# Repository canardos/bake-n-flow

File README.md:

# Bake-n-Flow

## Yet another (STM32F1-based) toaster reflow oven controller - PCB design and firmware

> [!Warning]
> This is personal project. It was built and works without issue for my purposes. It is made public here in case some part of it is useful to others, but **neither the hardware nor firmware have been rigorously tested**.

**Features:**

- Customizable profiles
- Reflow / baking operations
- Manual override controls
- Touch screen control

**This repo contains the firmware and PCB design.**

**See [custom electronics projects at DuckToast.com](https://www.ducktoast.com/blog/electronics-projects/) for full project details.**

https://github.com/canardos/bake-n-flow/assets/14832310/401d4c1e-f360-4829-90d8-4b5ea61bf341

## Build

The project uses the [PlatformIO](https://platformio.org/) dependency management/build system. If you have PlatformIO installed, executing the `run` command in the root folder *should* 🙏 be all that is required for a successful build. The `platformio.ini` file contains the required configuration and PlatformIO will download the required dependencies and toolchain.

**1. Clone repo and download submodules**

```shell
> git clone https://github.com/canardos/bake-n-flow.git
> cd bake-n-flow
> git submodule update --init
```

**2. Build firmware (PlatformIO must be installed)**

```shell
> pio run

Processing release (platform: ststm32; board: genericSTM32F103VD; framework: cmsis)
-----------------------------------------------------------------------------------
Verbose mode can be enabled via `-v, --verbose` option
CONFIGURATION: https://docs.platformio.org/page/boards/ststm32/genericSTM32F103VD.html
PLATFORM: ST STM32 (19.7.0) > STM32F103VD (64k RAM. 384k Flash)
HARDWARE: STM32F103VDT6 72MHz, 64KB RAM, 384KB Flash
DEBUG: Current (stlink) External (blackmagic, cmsis-dap, jlink, stlink)
PACKAGES:
 - framework-cmsis @ 2.50501.200527 (5.5.1)
 - framework-cmsis-stm32f1 @ 4.3.5
 - tool-ldscripts-ststm32 @ 0.2.0
 - toolchain-gccarmnoneeabi @ 1.120301.0 (12.3.1)
LDF: Library Dependency Finder -> https://bit.ly/configure-pio-ldf
LDF Modes: Finder ~ chain, Compatibility ~ soft
Found 4 compatible libraries
Scanning dependencies...
Dependency Graph
|-- libpekin @ 0.2.1
|-- libpekin_stm32
Building in release mode
Compiling piobuild/build/release/FrameworkCMSIS/gcc/startup_stm32f103xe.o
...
...
...
Archiving piobuild/build/release/lib7bf/libpekin_stm32.a
Indexing piobuild/build/release/lib7bf/libpekin_stm32.a
Archiving piobuild/build/release/lib72d/libpekin.a
Indexing piobuild/build/release/lib72d/libpekin.a
Linking piobuild/build/release/firmware.elf
Checking size piobuild/build/release/firmware.elf
Advanced Memory Usage is available via "PlatformIO Home > Project Inspect"
RAM:   [========= ]  95.0% (used 62248 bytes from 65536 bytes)
Flash: [=====     ]  50.5% (used 198660 bytes from 393216 bytes)
============================= [SUCCESS]
```

**3. Upload to device**

Similarly, use `pio run --target upload` to upload the firmware to the device. You'll likely need to update the upload settings in `platformio.ini` to reflect your settings, or use your own upload tool.

```shell
> pio run --target upload

Configuring upload protocol...
AVAILABLE: blackmagic, dfu, jlink, serial, stlink
CURRENT: upload_protocol = stlink
Uploading piobuild/build/release/firmware.elf
xPack OpenOCD, x86_64 Open On-Chip Debugger 0.10.0+dev-00378-ge5be992df (2020-06-26-09:27)
Licensed under GNU GPL v2
For bug reports, read
        http://openocd.org/doc/doxygen/bugs.html
debug_level: 1

hla_swd
target halted due to debug-request, current mode: Thread
xPSR: 0x01000000 pc: 0x0800108c msp: 0x20010000
** Programming Started **
** Programming Finished **
** Verify Started **
** Verified OK **
** Resetting Target **
shutdown command invoked
======================== [SUCCESS] Took 12.58 seconds =================================
```

**4. [optional] Create project files for IDE**

If you want to view/edit the project in your favorite IDE, use PlatformIO to generate the appropriate setup/workspace files and then import the project in the IDE:

```shell
> pio project init --ide [atom|clion|codeblocks|eclipse|emacs|netbeans|qtcreator|sublimetext|vim|visualstudio|vscode]
```

See the [PlatformIO documentation](https://docs.platformio.org) for further details.

### Using an alternate build system

**Platform dependencies**

If you wish to use a different build system, you will need:

| | |
|-|-|
| ST STM32 CMSIS headers | Peripheral/register definitions |
| CMSIS headers/source | CMSIS HAL functionality - SysTick_Config, NVIC_xxx etc.|
| CMSIS Cortex-M3 system source | `SystemInit()`/`SystemCoreClockUpdate()` implementation and `SystemCoreClock`|
| Startup source file | ASM file containing the startup code and vector table |
| Linker script | Tells the linker how to setup everything in flash/SRAM |

All of these are available in the [STM32 SDK](https://www.st.com/en/development-tools/stm32-software-development-tools.html) available from ST Micro.

**Compiling / linking**

`platformio.ini` lists the required compiler flags. Be sure to use `--specs=nano.specs` and `--specs=nosys.specs` when linking using your own tools, as the standard lib is be too large and is not used.

### Compiler

The project was compiled and tested with ~~`gcc-arm-none-eabi 9.2.1`~~ `gcc-arm-none-eabi 12.3.1`. It should work with any later GCC version and possibly with other compilers. The code contains some GCC flags and some C99 VLAs.

### Target requirements

| | |
|-|-|
|MCU  | STM32F103 with FSMC |
|Flash| >195kb              |
|SRAM | >61kb               |

It may be possible to get by with less SRAM by using a smaller drawing buffer (currently 40 lines - 38.4 kb)

## Dependencies

**CMSIS**

PlatformIO should automatically include/link the correct headers/sources from the STM32 SDK.

**LVGL**

[LVGL](https://github.com/lvgl/lvgl) v5.3 (git commit `9f216a55be65ec05c477ac55f73a6efad50f7680`) is used. It is included ~~as a Git submodule~~ in the`src/lvgl` folder.

**Libpekin**

[Libpekin](https://github.com/canardos/libpekin) is a collection of shared MCU-related code resulting from this and other projects. It's included as a Git submodule in the `lib` folder. PlatformIO will include the `lib` subfolders automatically.

## Hardware - PCB

The PCB was designed with KiCad v.5, but the files have been upgraded to v.7 and are located in `/hardware/pcb`. Gerber output for the first and only revision is located in `/hardware/pcb/plots`.

**The design contains minor errors** that should be fixed if it is (re)produced. See the [blog post here](https://www.ducktoast.com/blog/electronics-projects/reflow-oven/building-a-toaster-reflow-oven-part-3-manufacturing/#pcb-errors-and-things-i-would-have-done-differently) for details.

## Folder structure

```
BakeNFlow
|
+--hardware          | KiCad schematic and board design files
|
+--lib
|  |
|  +--libpekin       | Libpekin platform independent code
|  +--libpekin_stm32 | Libpekin STM32 specific code
|
+--src
|  |
|  +--audio_samples  | Audio sample data
|  +--devices        | Hardware device drivers
|  +--lvgl           | LVGL project
|  +--lvgl_driver    | Display/touch driver for LVGL
|  +--oven           | Oven hardware interface and state management
|  +--reflow         | Reflow data structures and state management
|  +--hal            | (exception handlers etc.)
|  +--ui             | UI code for LVGL
|
|--test              | No tests in use
```

## License

This software is available under the [MIT license](https://opensource.org/license/MIT).

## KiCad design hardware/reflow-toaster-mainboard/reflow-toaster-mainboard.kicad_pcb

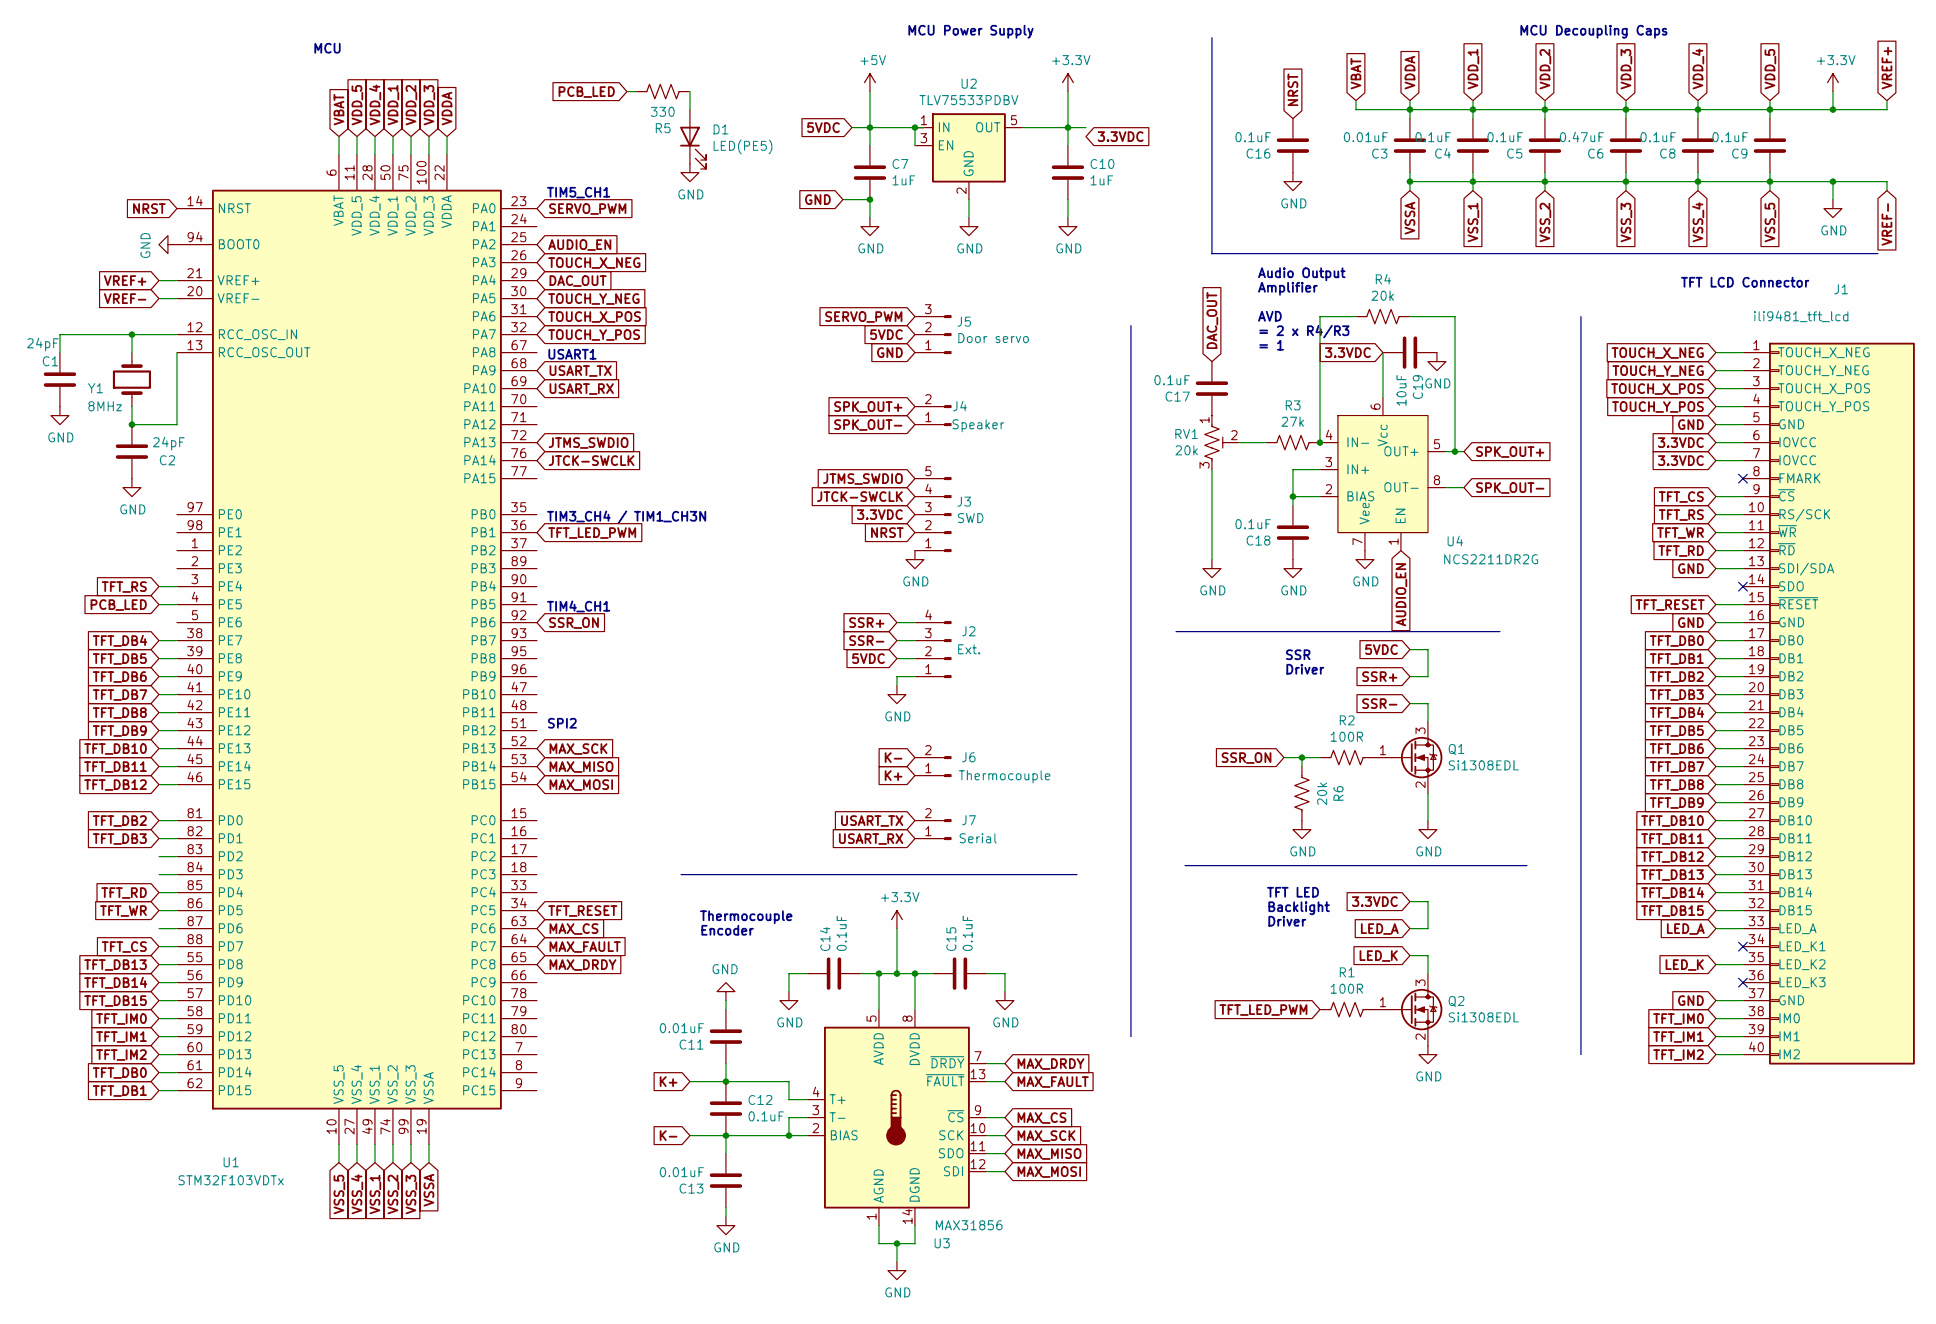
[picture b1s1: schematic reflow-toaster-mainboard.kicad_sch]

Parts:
C1, C2: 24pF; C_0402_1005Metric
C3, C11, C13: 0.01uF; C_0402_1005Metric
C4, C5, C8, C9, C12, C14, C15, C16, C17, C18: 0.1uF; C_0402_1005Metric
C6: 0.47uF; C_0402_1005Metric
C7, C10: 1uF; C_0402_1005Metric
C19: 10uF; C_0805_2012Metric
D1: LED(PE5); D_0603_1608Metric
J1: ili9481_tft_lcd; Hirose_FH12-40S-0.5SH_1x40-1MP_P0.50mm_Horizontal
J2: Ext.; PinHeader_1x04_P2.54mm_Horizontal
J3: SWD; PinHeader_1x05_P2.54mm_Horizontal
J4: Speaker; JST_PH_S2B-PH-K_1x02_P2.00mm_Horizontal
J5: Door servo; PinHeader_1x03_P2.54mm_Horizontal
J6: Thermocouple; PinHeader_1x02_P2.54mm_Horizontal
J7: Serial; PinHeader_1x02_P1.27mm_Horizontal
Q1, Q2: Si1308EDL; SOT-323_SC-70
R1, R2: 100R; R_0603_1608Metric
R3: 27k; R_0603_1608Metric
R4, R6: 20k; R_0603_1608Metric
R5: 330; R_0603_1608Metric
RV1: 20k; Trimmer_Potentiometer_Panasonic_EVM3W
U1: STM32F103VDTx; LQFP-100_14x14mm_P0.5mm
U2: TLV75533PDBV; SOT-23-5
U3: MAX31856; TSSOP-14_4.4x5mm_P0.65mm
U4: NCS2211DR2G; SOIC-8_3.9x4.9mm_P1.27mm
Y1: 8MHz; Crystal_SMD_7050-2Pin_7.0x5.0mm_HandSoldering

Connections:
5VDC: C7.1, J2.2, J2.4, J5.2, U2.1 (IN), U2.3 (EN)
AUDIO_EN: U1.25 (PA2), U4.1 (EN)
DAC_OUT: C17.2, U1.29 (PA4)
GND: C1.1, C2.1, C3.1, C4.1, C5.1, C6.1, C7.2, C8.1, C9.1, C10.2, C11.2, C13.1, C14.1, C15.2, C16.1, C18.1, C19.1, D1.1 (K), J1.5 (GND), J1.13 (SDI/SDA), J1.16 (GND), J1.37 (GND), J2.1, J3.1, J5.1, Q1.2 (S), Q2.2 (S), R6.1, RV1.3, U1.10 (VSS_5), U1.19 (VSSA), U1.20 (VREF-), U1.27 (VSS_4), U1.49 (VSS_1), U1.74 (VSS_2), U1.94 (BOOT0), U1.99 (VSS_3), U2.2 (GND), U3.1 (AGND), U3.14 (DGND), U4.7 (Vee)
JTCK-SWCLK: J3.4, U1.76 (PA14)
JTMS_SWDIO: J3.5, U1.72 (PA13)
K+: C11.1, C12.1, J6.1, U3.4 (T+)
K-: C12.2, C13.2, J6.2, U3.2 (BIAS), U3.3 (T-)
LED_K: J1.35 (LED_K2), Q2.3 (D)
MAX_CS: U1.63 (PC6), U3.9 (~CS)
MAX_DRDY: U1.65 (PC8), U3.7 (~DRDY)
MAX_FAULT: U1.64 (PC7), U3.13 (~FAULT)
MAX_MISO: U1.53 (PB14), U3.11 (SDO)
MAX_MOSI: U1.54 (PB15), U3.12 (SDI)
MAX_SCK: U1.52 (PB13), U3.10 (SCK)
NRST: C16.2, J3.2, U1.14 (NRST)
unnamed: C1.2, U1.12 (RCC_OSC_IN), Y1.2
unnamed: C2.2, U1.13 (RCC_OSC_OUT), Y1.1
unnamed: C17.1, RV1.1
unnamed: C18.2, U4.2 (BIAS), U4.3 (IN+)
unnamed: D1.2 (A), R5.2
unnamed: Q1.1 (G), R2.1
unnamed: Q2.1 (G), R1.1
unnamed: R3.1, R4.2, U4.4 (IN-)
unnamed: R3.2, RV1.2
PCB_LED: R5.1, U1.4 (PE5)
SERVO_PWM: J5.3, U1.23 (PA0)
SPK_OUT+: J4.2, R4.1, U4.5 (OUT+)
SPK_OUT-: J4.1, U4.8 (OUT-)
SSR-: J2.3, Q1.3 (D)
SSR_ON: R2.2, R6.2, U1.92 (PB6)
TFT_CS: J1.9 (~CS), U1.88 (PD7)
TFT_DB0: J1.17 (DB0), U1.61 (PD14)
TFT_DB1: J1.18 (DB1), U1.62 (PD15)
TFT_DB2: J1.19 (DB2), U1.81 (PD0)
TFT_DB3: J1.20 (DB3), U1.82 (PD1)
TFT_DB4: J1.21 (DB4), U1.38 (PE7)
TFT_DB5: J1.22 (DB5), U1.39 (PE8)
TFT_DB6: J1.23 (DB6), U1.40 (PE9)
TFT_DB7: J1.24 (DB7), U1.41 (PE10)
TFT_DB8: J1.25 (DB8), U1.42 (PE11)
TFT_DB9: J1.26 (DB9), U1.43 (PE12)
TFT_DB10: J1.27 (DB10), U1.44 (PE13)
TFT_DB11: J1.28 (DB11), U1.45 (PE14)
TFT_DB12: J1.29 (DB12), U1.46 (PE15)
TFT_DB13: J1.30 (DB13), U1.55 (PD8)
TFT_DB14: J1.31 (DB14), U1.56 (PD9)
TFT_DB15: J1.32 (DB15), U1.57 (PD10)
TFT_IM0: J1.38 (IM0), U1.58 (PD11)
TFT_IM1: J1.39 (IM1), U1.59 (PD12)
TFT_IM2: J1.40 (IM2), U1.60 (PD13)
TFT_LED_PWM: R1.2, U1.36 (PB1)
TFT_RD: J1.12 (~RD), U1.85 (PD4)
TFT_RESET: J1.15 (~RESET), U1.34 (PC5)
TFT_RS: J1.10 (RS/SCK), U1.3 (PE4)
TFT_WR: J1.11 (~WR), U1.86 (PD5)
TOUCH_X_NEG: J1.1 (TOUCH_X_NEG), U1.26 (PA3)
TOUCH_X_POS: J1.3 (TOUCH_X_POS), U1.31 (PA6)
TOUCH_Y_NEG: J1.2 (TOUCH_Y_NEG), U1.30 (PA5)
TOUCH_Y_POS: J1.4 (TOUCH_Y_POS), U1.32 (PA7)
USART_RX: J7.1, U1.69 (PA10)
USART_TX: J7.2, U1.68 (PA9)

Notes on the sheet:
MCU
TFT LED Backlight Driver
TIM5_CH1
Thermocouple Encoder
MCU Decoupling Caps
SSR Driver
SPI2
TFT LCD Connector
Audio Output Amplifier AVD = 2 x R4/R3 = 1
TIM4_CH1
USART1
TIM3_CH4 / TIM1_CH3N
MCU Power Supply

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
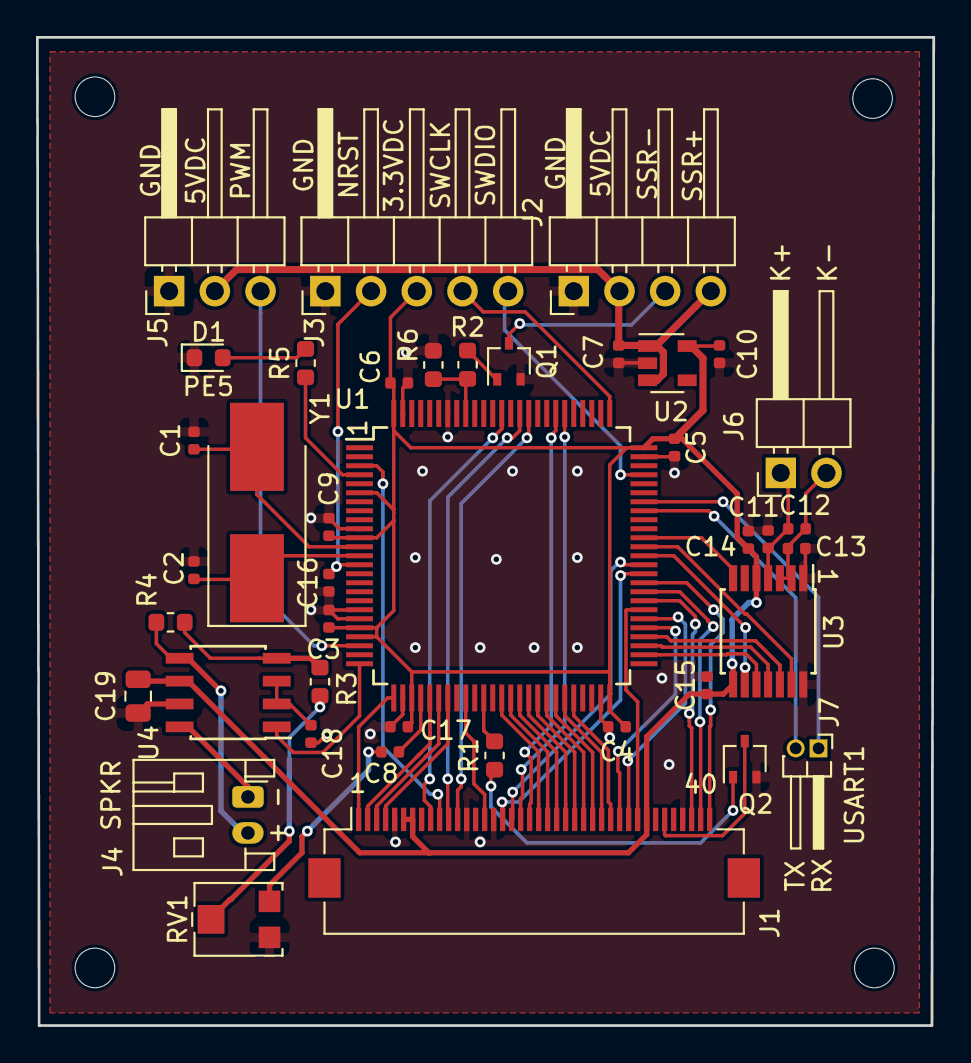
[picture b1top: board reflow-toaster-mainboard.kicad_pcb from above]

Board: 2 copper layers, 49.8 x 54.9 mm, 41 parts (0 on the bottom side), 63 nets.

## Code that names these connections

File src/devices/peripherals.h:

#ifndef MYGPIO_H_
#define MYGPIO_H_

#include <cstdint>

#include "lp_clock_stm32f1xx.h"
#include "lp_fsmc_stm32f1xx.h"
#include "lp_pins_stm32f1xx.h"

/*
 * STM32F103V[C/D/E]
 *
 * -----------------------
 * TFT LCD
 * -----------------------
 * TFT_Reset   : PC5
 *
 * TFT_RD      : PD4 (FSMC_NOE)
 * TFT_WR      : PD5 (FSMC_NWE)
 * TFT_CS      : PD7 (FSMC_NE1)
 * TFT_RS      : PE4 (FSMC_A20)
 *
 * TFT_D0      : PD14 (FSMC_D0)
 * TFT_D1      : PD15 (FSMC_D1)
 * TFT_D2      : PD0  (FSMC_D2)
 * TFT_D3      : PD1  (FSMC_D3)
 * TFT_D4      : PE7  (FSMC_D4)
 * TFT_D5      : PE8  (FSMC_D5)
 * TFT_D6      : PE9  (FSMC_D6)
 * TFT_D7      : PE10 (FSMC_D7)
 * TFT_D8      : PE11 (FSMC_D8)
 * TFT_D9      : PE12 (FSMC_D9)
 * TFT_D10     : PE13 (FSMC_D10)
 * TFT_D11     : PE14 (FSMC_D11)
 * TFT_D12     : PE15 (FSMC_D12)
 * TFT_D13     : PD8  (FSMC_D13)
 * TFT_D14     : PD9  (FSMC_D14)
 * TFT_D15     : PD10 (FSMC_D15)
 *
 * TFT_IM0     : PD11
 * TFT_IM1     : PD12
 * TFT_IM2     : PD13
 *
 * -----------------------
 * Resistive Touchscreen
 * -----------------------
 * TOUCH_X_NEG : PA3
 * TOUCH_X_POS : PA5 (ADC1/2 in5)
 * TOUCH_Y_NEG : PA6
 * TOUCH_Y_POS : PA7 (ADC1/2 in7)
 *
 * -----------------------
 * MAX31856 SPI Connection
 * -----------------------
 * MAX_CS      : PC6
 * MAX_SCK     : PB13 (SPI2)
 * MAX_MISO    : PB14 (SPI2)
 * MAX_MOSI    : PB15 (SPI2)
 * MAX_DDRY    : PC8
 * MAX_FAULT   : PC7
 *
 * -----------------------
 * Other
 * -----------------------
 * AUDIO_EN    : PA2
 * AUDIO_OUT   : PA4 (DAC)
 * SERVO_PWM   : PA0 (TIM5_CH1)
 * TFT_LED_PWM : PB1 (TIM3_CH4 / TIM1_CH3N)
 * SSR_PWM     : PB6 (TIM4_CH1)
 * PCB_LED     : PE5
 */

namespace PinNb {

inline constexpr uint8_t pcb_led = 5;
inline constexpr uint8_t audio_en = 2;
inline constexpr uint8_t audio_out = 4;

// SPI for MAX31856
inline constexpr uint8_t max_spi_cs = 6;

// TFT LCD (ex FSMC)
inline constexpr uint8_t im0 = 11;
inline constexpr uint8_t im1 = 12;
inline constexpr uint8_t im2 = 13;
inline constexpr uint8_t tft_reset = 5;
inline constexpr uint8_t tft_cs = 7;
inline constexpr uint8_t tft_rd = 4;
inline constexpr uint8_t tft_wr = 5;

// PWM
inline constexpr uint8_t door_servo_pwm = 0;
inline constexpr uint8_t ssr_pwm = 6;
inline constexpr uint8_t tft_led_pwm = 1;

}

namespace pins {

static inline libp_stm32::PinE<PinNb::pcb_led> pcb_led;
static inline libp_stm32::PinA<PinNb::audio_en> audio_en;

static inline libp_stm32::PinC<PinNb::max_spi_cs> max_spi_cs;

// TFT LCD (ex FSMC)
static inline libp_stm32::PinD<PinNb::im0> tft_im0;
static inline libp_stm32::PinD<PinNb::im1> tft_im1;
static inline libp_stm32::PinD<PinNb::im2> tft_im2;
static inline libp_stm32::PinC<PinNb::tft_reset> tft_reset;

}

namespace Details {
inline __attribute__((always_inline))
void initGpio()
{
    using namespace libp_stm32;

    clk::enable<
            clk::Apb2::iopa,
            clk::Apb2::iopb,
            clk::Apb2::iopc,
            clk::Apb2::iopd,
            clk::Apb2::iope>();

    pins::pcb_led.clear();
    pins::audio_en.clear();
    pins::max_spi_cs.clear();
    pins::tft_im0.clear();
    pins::tft_im1.clear();
    pins::tft_im2.clear();
    pins::tft_reset.clear();

    GpioA::setOutputs<OutputMode::pushpull, OutputSpeed::low,
            PinNb::audio_en >();

    GpioE::setOutputs<OutputMode::pushpull, OutputSpeed::low,
            PinNb::pcb_led >();

    GpioC::setOutputs<OutputMode::pushpull, OutputSpeed::low,
            PinNb::tft_reset,
            PinNb::max_spi_cs >();

    // SPI setup in thermocouple init

    GpioD::setOutputs<OutputMode::pushpull, OutputSpeed::low,
            PinNb::im0,
            PinNb::im1,
            PinNb::im2 >();

    // FSMC

    GpioD::setOutputs<OutputMode::alt_pushpull, OutputSpeed::high,
            8, 9, 10, 14, 15, 0, 1, PinNb::tft_rd, PinNb::tft_wr, PinNb::tft_cs >();

    GpioE::setOutputs<OutputMode::alt_pushpull, OutputSpeed::high,
            4, 7, 8, 9, 10, 11, 12, 13, 14, 15 >();

    // DAC

    GpioA::setInputs<InputMode::analog,
            PinNb::audio_out >();

    // USART

    def_pin::usart1_tx.setAsOutput(OutputMode::alt_pushpull, OutputSpeed::low);
    def_pin::usart1_rx.setAsInput(libp_stm32::InputMode::floating);
}

inline __attribute__((always_inline))
void initFsmcSram()
{
    constexpr libp_stm32::fsmc::SramNorCfg cfg = []() {
        libp_stm32::fsmc::Config config;

        config.timing.addr_setup = 5;
        config.timing.addr_hold = 2;
        config.timing.data_phase_dur = 3;

        config.addr_data_mux = false;
        config.mem_type = libp_stm32::fsmc::Config::MemType::sram;
        config.flash_access_en = false;

        return config.makeConfig();
    }();
    libp_stm32::clk::enable<libp_stm32::clk::Ahb::fsmc>();
    libp_stm32::fsmc::NorSram<1>::init(cfg);
    libp_stm32::fsmc::nadvDisconnected(); // don't use NADV output
}
} // namespace Details

inline __attribute__((always_inline))
void initPeripherals()
{
    Details::initGpio();
    Details::initFsmcSram();
}

#endif /* MYGPIO_H_ */

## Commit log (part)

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2019-03-17 Initial commit of firmware and PCB
2024-03-17 Update readme links
2024-04-04 Update readme build info
2024-04-04 Fix UI video in README.md
2024-04-04 Update PCB to KiCad v7

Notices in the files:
hardware/reflow-toaster-mainboard/reflow-toaster-mainboard.kicad_pcb:
© 2019
